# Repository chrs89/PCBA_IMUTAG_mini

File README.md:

# PCBA IMU Tag

A compact IMU tag PCB designed in KiCad.

## Preview

## Project files

- `*.kicad_pro` — KiCad project file
- `*.kicad_sch` — schematic
- `*.kicad_pcb` — PCB layout

## Status

Work in progress.

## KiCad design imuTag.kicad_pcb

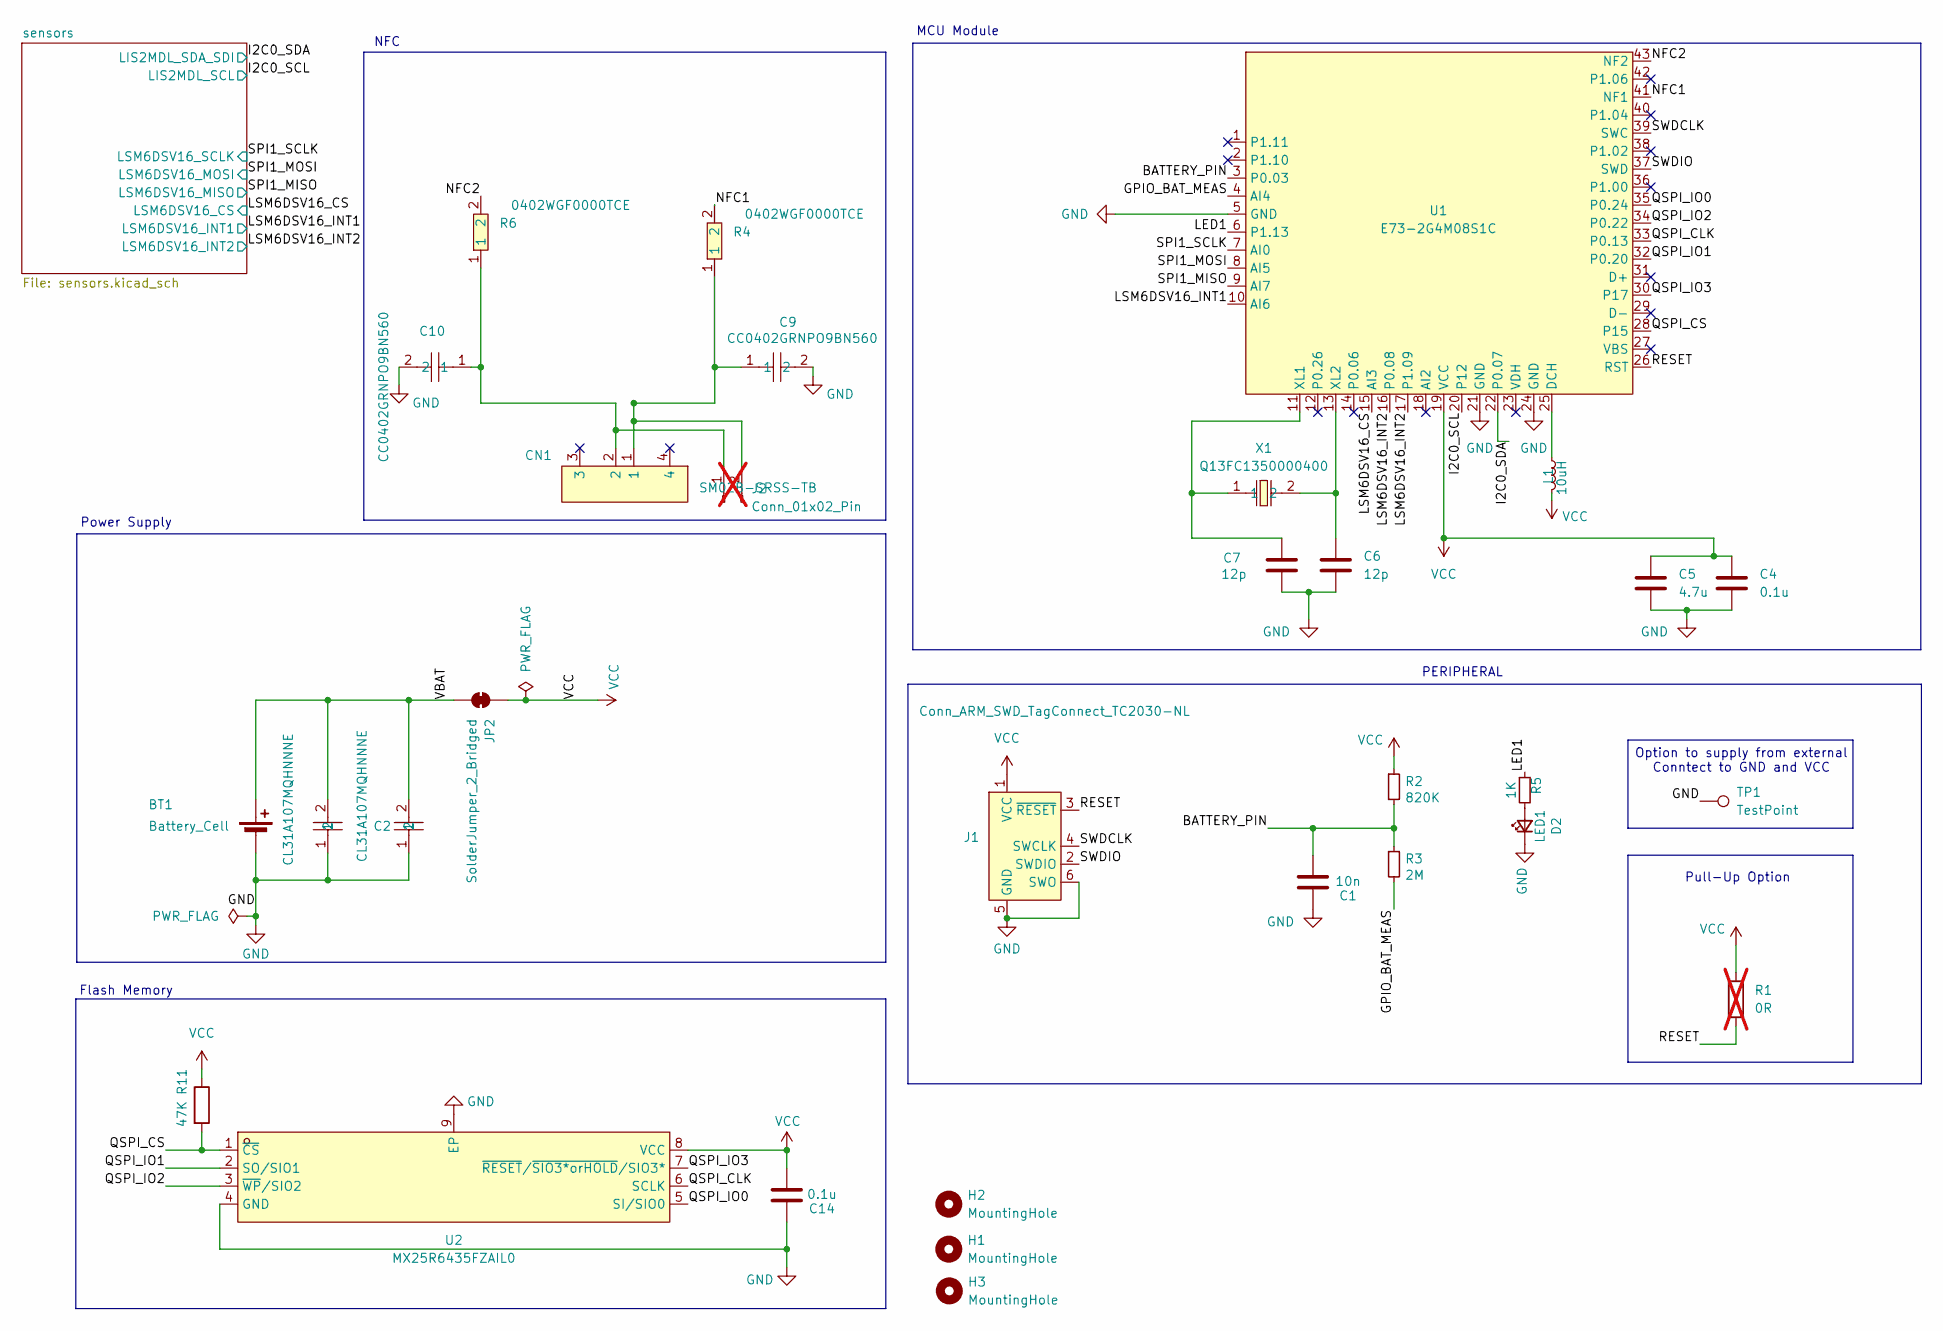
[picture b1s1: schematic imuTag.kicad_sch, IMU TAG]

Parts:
BT1: Battery_Cell; CR2032_Custom_Contacts_SMD_AirTagStyle
C1: 10n; C_0402_1005Metric
C2, C8: CL31A107MQHNNNE; C1206; MPN CL31A107MQHNNNE; LCSC Part C15008
C4: 0.1u; C_0603_1608Metric_Pad1.08x0.95mm_HandSolder
C5: 4.7u; C_0603_1608Metric
C6, C7: 12p; C_0402_1005Metric
C9, C10: CC0402GRNPO9BN560; C0402; MPN CC0402GRNPO9BN560; LCSC Part C526989
C14: 0.1u; C_0402_1005Metric
CN1: SM02B-SRSS-TB; CONN-SMD_2P-P1.00_SM02B-SRSS-TB-LF-SN; MPN SM02B-SRSS-TB(LF)(SN); LCSC Part C160402
D2: LED1; LED_0603_1608Metric_Pad1.05x0.95mm_HandSolder
H1, H3: MountingHole; MountingHole_2.1mm
H2: MountingHole; Slot_1.2x3.0mm_NPTH
J1: Conn_ARM_SWD_TagConnect_TC2030-NL; Tag-Connect_TC2030-IDC-NL_2x03_P1.27mm_Vertical
J2: Conn_01x02_Pin; PinHeader_1x02_P1.27mm_Vertical; not fitted
JP2: SolderJumper_2_Bridged; SolderJumper-2_P1.3mm_Bridged2Bar_Pad1.0x1.5mm
L1: 10uH; L_0603_1608Metric_Pad1.05x0.95mm_HandSolder
R1: 0R; R_0805_2012Metric_Pad1.20x1.40mm_HandSolder; not fitted
R2: 820K; R_0402_1005Metric
R3: 2M; R_0402_1005Metric
R4: 0402WGF0000TCE; R_0402_1005Metric; MPN 0402WGF0000TCE; LCSC Part C17168
R5: 1K; R_0402_1005Metric
R6: 0402WGF0000TCE; R0402; MPN 0402WGF0000TCE; LCSC Part C17168
R11: 47K; R_0402_1005Metric
TP1: TestPoint; TestPoint_Pad_D1.0mm
U1: E73-2G4M08S1C; WIRELM-SMD_E73-2G4M08S1C; MPN E73-2G4M08S1C; LCSC Part C356849
U2: MX25R6435FZAIL0; WSON-8_L4.0-W4.0-P0.80-BL-EP-1; MPN MX25R6435FZAIL0; LCSC Part C2802847
X1: Q13FC1350000400; FC-135R_L3.2-W1.5; MPN Q13FC13500004; LCSC Part C32346

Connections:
/BATTERY_PIN: C1.2, R2.2, R3.1, U1.3 (P0.03)
/GPIO_BAT_MEAS: R3.2, U1.4 (AI4)
/I2C0_SCL: U1.20 (P12); also elsewhere on the board
/I2C0_SDA: U1.22 (P0.07); also elsewhere on the board
/LED1: R5.1, U1.6 (P1.13)
/LSM6DSV16_CS: U1.15 (AI3); also elsewhere on the board
/LSM6DSV16_INT1: U1.10 (AI6); also elsewhere on the board
/LSM6DSV16_INT2: U1.16 (P0.08), U1.17 (P1.09); also elsewhere on the board
/NFC1: R4.2, U1.41 (NF1)
/NFC2: R6.2, U1.43 (NF2)
/QSPI_CLK: U1.33 (P0.13), U2.6 (SCLK)
/QSPI_CS: R11.2, U1.28 (P15), U2.1 (~CS)
/QSPI_IO0: U1.35 (P0.24), U2.5 (SI/SIO0)
/QSPI_IO1: U1.32 (P0.20), U2.2 (SO/SIO1)
/QSPI_IO2: U1.34 (P0.22), U2.3 (~WP/SIO2)
/QSPI_IO3: U1.30 (P17), U2.7 (~RESET/~SIO3*orHOLD/SIO3*)
/RESET: J1.3 (~RESET), R1.2, U1.26 (RST)
/SPI1_MISO: U1.9 (AI7); also elsewhere on the board
/SPI1_MOSI: U1.8 (AI5); also elsewhere on the board
/SPI1_SCLK: U1.7 (AI0); also elsewhere on the board
/SWDCLK: J1.4 (SWCLK), U1.39 (SWC)
/SWDIO: J1.2 (SWDIO), U1.37 (SWD)
/VBAT: BT1.1 (+), C2.2, C8.2, JP2.1 (A)
GND: BT1.2 (-), C1.1, C2.1, C4.2, C5.2, C6.2, C7.2, C8.1, C9.2, C10.2, C14.1, D2.1 (K), J1.5 (GND), J1.6 (SWO), TP1.1, U1.5 (GND), U1.21 (GND), U1.24 (GND), U2.4 (GND), U2.9 (EP); also elsewhere on the board
unnamed: D2.2 (A), R5.2
unnamed: C10.1, CN1.2, J2.1, R6.1
unnamed: C9.1, CN1.1, J2.2, R4.1
unnamed: L1.1, U1.25 (DCH)
unnamed: C7.1, U1.11 (XL1), X1.1
unnamed: C6.1, U1.13 (XL2), X1.2
VCC: C4.1, C5.1, C14.2, J1.1 (VCC), JP2.2 (B), L1.2, R1.1, R2.1, R11.1, U1.19 (VCC), U2.8 (VCC); also elsewhere on the board

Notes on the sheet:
MCU Module
Power Supply
Pull-Up Option
NFC
Flash Memory
Option to supply from external Conntect to GND and VCC
PERIPHERAL

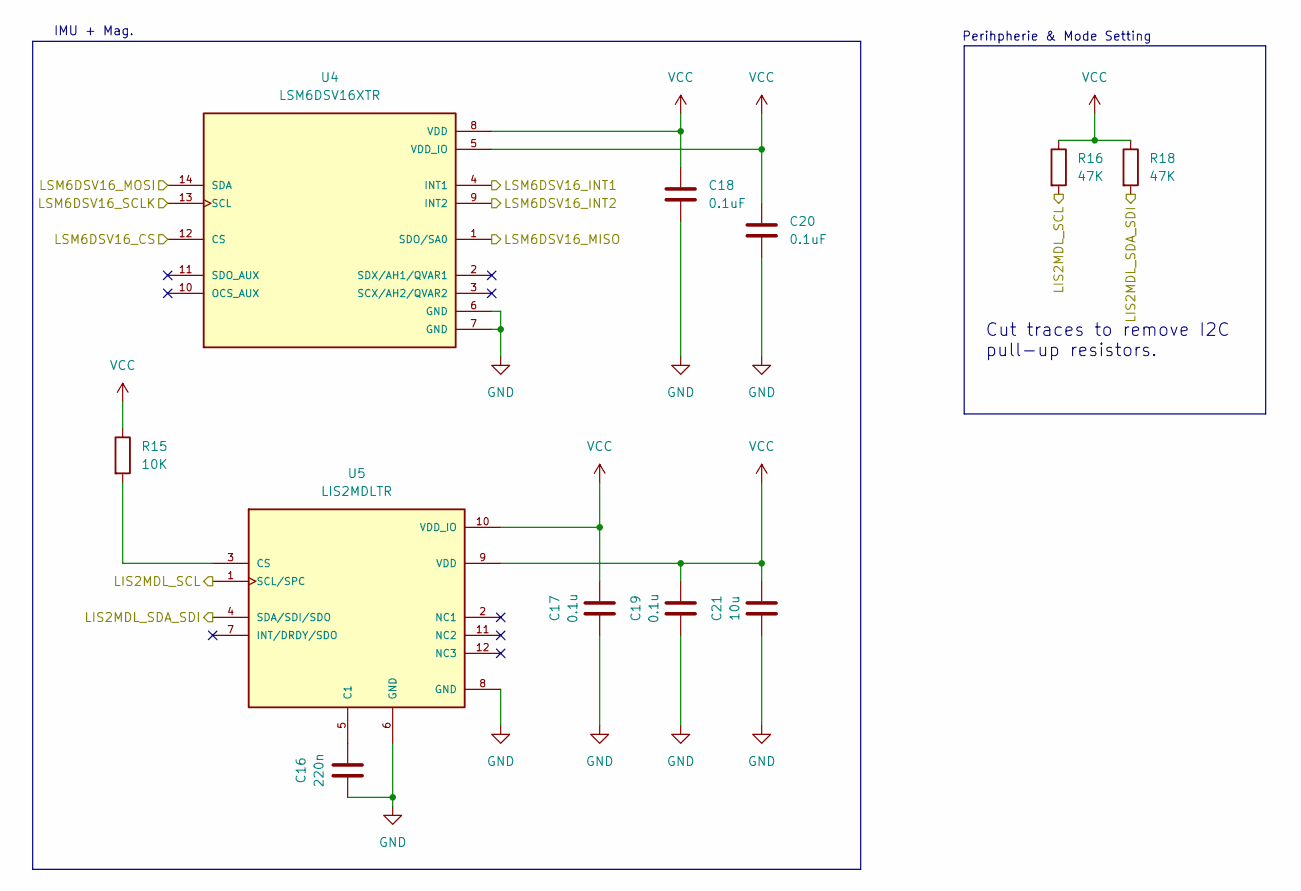
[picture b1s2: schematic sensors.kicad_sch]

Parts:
C16: 220n; C_0402_1005Metric
C17, C19: 0.1u; C_0402_1005Metric
C18, C20: 0.1uF; C_0402_1005Metric
C21: 10u; C_0603_1608Metric
R15: 10K; R_0402_1005Metric
R16, R18: 47K; R_0402_1005Metric
U4: LSM6DSV16XTR; LGA-14_L3.0-W2.5-P0.50-BR; PARTREV 4
U5: LIS2MDLTR; VLGA-12_L2.0-W2.0-P0.50-BL; PARTREV Rev 5

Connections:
/I2C0_SCL: R16.2, U5.1 (SCL/SPC); also elsewhere on the board
/I2C0_SDA: R18.2, U5.4 (SDA/SDI/SDO); also elsewhere on the board
/LSM6DSV16_CS: U4.12 (CS); also elsewhere on the board
/LSM6DSV16_INT1: U4.4 (INT1); also elsewhere on the board
/LSM6DSV16_INT2: U4.9 (INT2); also elsewhere on the board
/SPI1_MISO: U4.1 (SDO/SA0); also elsewhere on the board
/SPI1_MOSI: U4.14 (SDA); also elsewhere on the board
/SPI1_SCLK: U4.13 (SCL); also elsewhere on the board
GND: C16.1, C17.1, C18.2, C19.1, C20.2, C21.1, U4.6 (GND), U4.7 (GND), U5.6 (GND), U5.8 (GND); also elsewhere on the board
unnamed: C16.2, U5.5 (C1)
unnamed: R15.2, U5.3 (CS)
VCC: C17.2, C18.1, C19.2, C20.1, C21.2, R15.1, R16.1, R18.1, U4.5 (VDD_IO), U4.8 (VDD), U5.9 (VDD), U5.10 (VDD_IO); also elsewhere on the board

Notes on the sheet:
Cut traces to remove I2C pull-up resistors.
Perihpherie & Mode Setting
IMU + Mag.

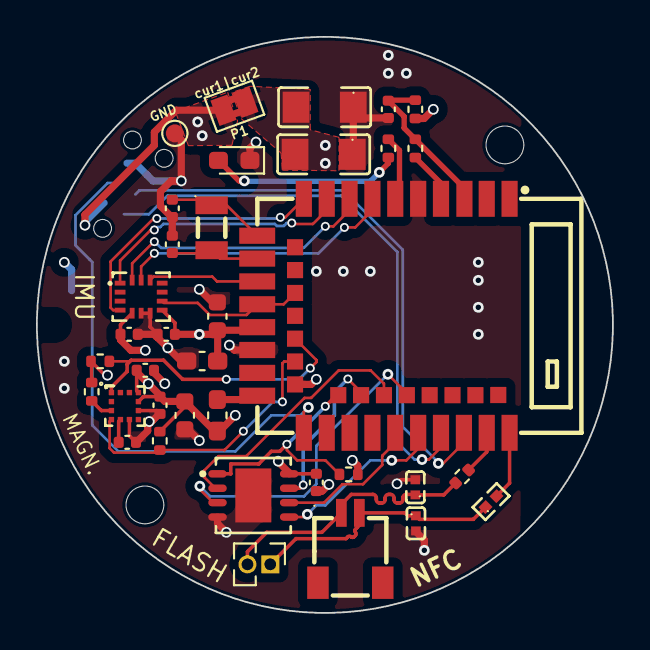
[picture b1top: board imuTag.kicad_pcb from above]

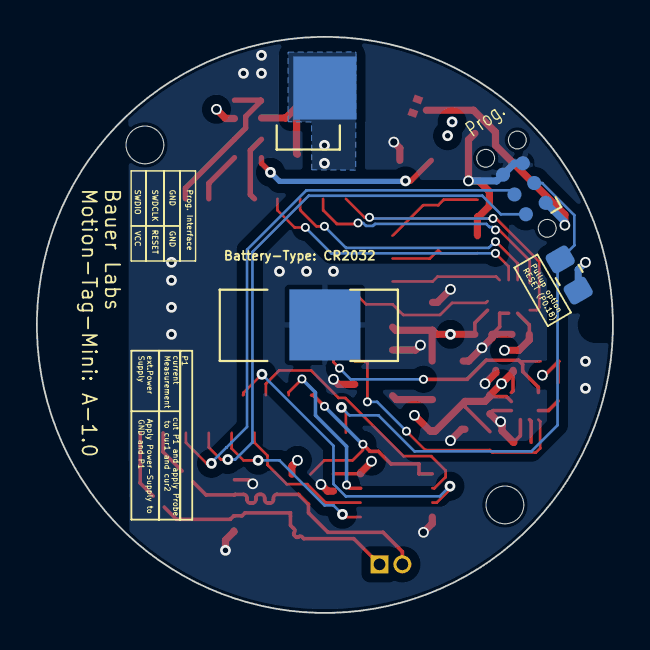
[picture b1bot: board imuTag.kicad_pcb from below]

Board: 4 copper layers, 32.0 x 32.0 mm, 42 parts (3 on the bottom side), 33 nets.

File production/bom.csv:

Designator,Footprint,Quantity,Value,LCSC Part #
BT1,CR2032_Custom_Contacts_SMD_AirTagStyle,1,Battery_Cell,
C1,0402,1,10n,
"C14, C17, C19",0402,3,0.1u,
C16,0402,1,220n,
"C18, C20",0402,2,0.1uF,
"C2, C8",C1206,2,CL31A107MQHNNNE,C15008
C21,0603,1,10u,
C4,0603,1,0.1u,
C5,0603,1,4.7u,
"C6, C7",0402,2,12p,
D2,0603,1,LED1,
L1,0603,1,10uH,
R1,0805,1,0R,
"R11, R16, R18",0402,3,47K,
R15,0402,1,10K,
R2,0402,1,820K,
R3,0402,1,2M,
R5,0402,1,1K,
TP1,TestPoint_Pad_D1.0mm,1,TestPoint,
U1,WIRELM-SMD_E73-2G4M08S1C,1,E73-2G4M08S1C,C356849
U2,WSON-8_L4.0-W4.0-P0.80-BL-EP-1,1,MX25R6435FZAIL0,C2802847
U4,LGA-14_L3.0-W2.5-P0.50-BR,1,LSM6DSV16XTR,
U5,VLGA-12_L2.0-W2.0-P0.50-BL,1,LIS2MDLTR,
Y2,Crystal_SMD_3215-2Pin_3.2x1.5mm,1,Crystal,

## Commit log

2026-05-15 Initial KiCad PCB project IMU-Tag
2026-05-15 Add README with PCBA image
2026-05-15 Add copper zones before routing
2026-05-15 Fix footprint DRC issues before routing
2026-05-15 Route power traces
2026-05-16 Optimize power path component arrangement
2026-05-16 Routing of critical Paths, Finalizing Zones
2026-05-16 Route critical nets and finalize zones
2026-05-16 Save current QSPI routing cleanup
2026-05-16 finalize power routing and decoupling capacitors
2026-05-16 Save current routing work
2026-05-16 Save routing work before rebase
2026-05-16 Ignore KiCad temporary files
2026-05-16 draw Important Tracks
2026-05-16 Ignore generated KiCad and FreeRouting files
2026-05-16 Add autorouted PCB layout
2026-05-17 Complete routed PCB layout
2026-05-17 Finalize PCB for production
2026-05-17 Add 32 kHz crystal and load capacitors
2026-05-17 Exclude fabrication toolkit plugin files
2026-05-17 Ignore plugin resources folder
2026-05-17 Ignore plugin resources
2026-05-17 Add debug pins AI0 to AI4 to layout
2026-05-17 Exclude plugin files from AI0 to AI4 release
2026-05-17 Update KiCad project local settings
2026-05-17 Update PCB layout
2026-05-17 Exclude plugin files from main
2026-05-17 updated pcba picture
2026-06-15 feat: imuTag mini PCBA v1.0 – initial release
    PCB layout, schematics (imuTag + sensors), custom EasyEDA symbol/footprint libraries with 3D models, design rules, and production outputs (BOM, placement, netlist).
2026-06-15 feat: import Spectra auto-route session into PCB layout
    Applied Freerouting/Spectra session to imuTag.kicad_pcb, updating copper traces from the auto-router result.
2026-06-15 feat: finalize schematic wiring
    Completed all net connections across imuTag and sensors schematics. Design is electrically complete and ready for layout review.
2026-06-15 fix: minor wiring corrections under v1.2
2026-06-16 fix: wire unconnected pin and clear DRC exclusions
2026-06-17 feat: optimize LIS2MDL layout for magnetic integrity
2026-06-17 docs: update 3D render for v1.3 layout
2026-06-17 production: regenerate fabrication files for v1.3
2026-06-17 chore: ignore production folder, untrack generated fab files
2026-06-18 feat: add NFC antenna support via E73-2G4M08S1C
    - Add NFC matching network (ESD protection, 100pF tuning caps)
    - Add hybrid antenna connector (JST SH 1.0mm + hand-solder test pads)
    - Add 4-layer keepout zones around NFC traces and antenna feed
    - Route and length-balance NFC1/NFC2 traces
2026-06-18 docs: update 3D render for v1.4 NFC antenna layout
